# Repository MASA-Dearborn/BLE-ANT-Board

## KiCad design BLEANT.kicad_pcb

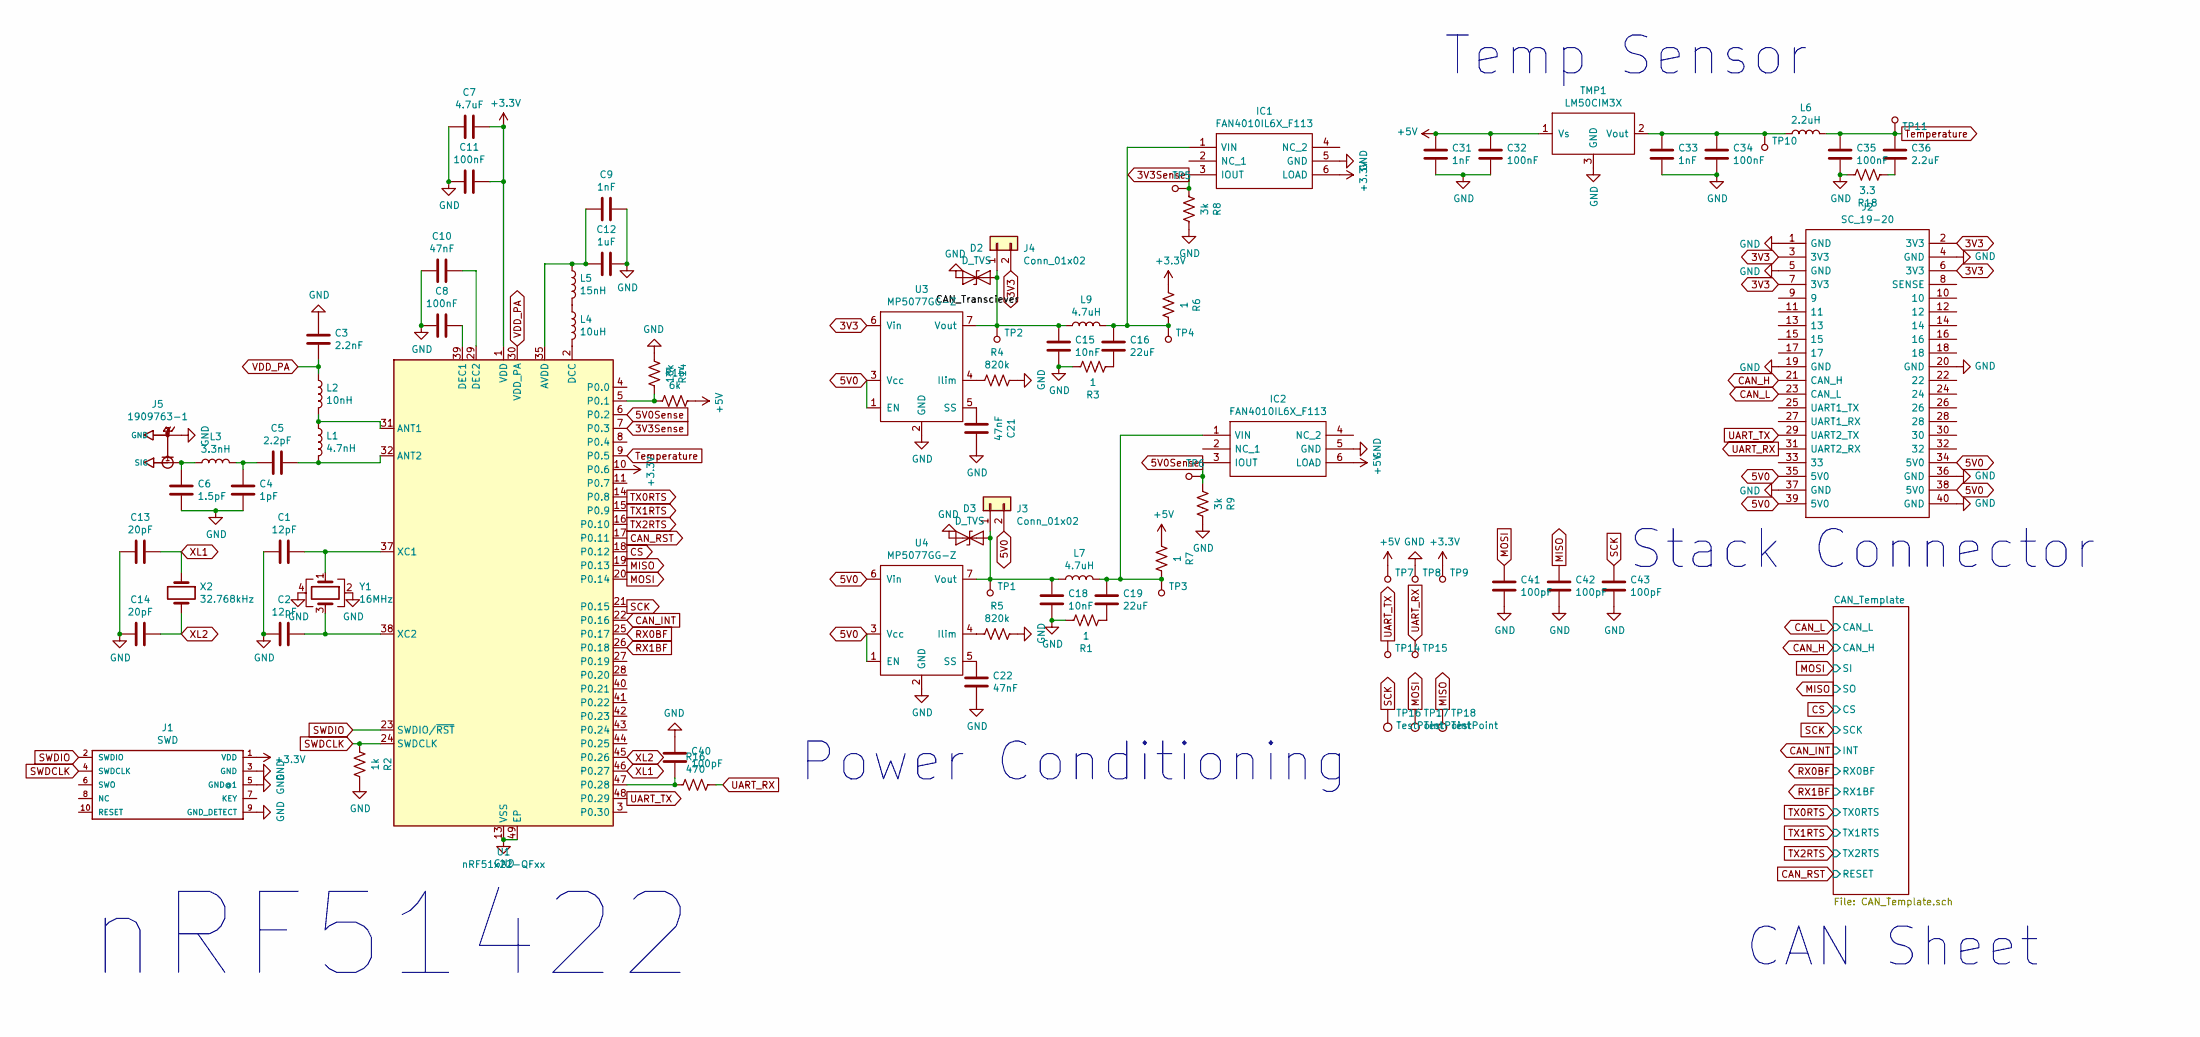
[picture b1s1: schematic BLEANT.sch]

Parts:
C1, C2: 12pF; C_0402_1005Metric
C3: 2.2nF; C_0402_1005Metric
C4: 1pF; C_0402_1005Metric
C5: 2.2pF; C_0402_1005Metric
C6: 1.5pF; C_0402_1005Metric
C7: 4.7uF; C_0402_1005Metric
C8, C11, C32, C34, C35: 100nF; C_0402_1005Metric
C9, C31, C33: 1nF; C_0402_1005Metric
C10, C21, C22: 47nF; C_0402_1005Metric
C12: 1uF; C_0402_1005Metric
C13, C14: 20pF; C_0402_1005Metric
C15, C18: 10nF; C_0402_1005Metric
C16, C19: 22uF; C_0805_2012Metric
C36: 2.2uF; C_0402_1005Metric
C40, C41, C42, C43: 100pF; C_0402_1005Metric
D2, D3: D_TVS; D_SOD-523
IC1, IC2: FAN4010IL6X_F113; 6-LEAD_MICROPAK; Manufacturer_Part_Number FAN4010IL6X_F113; Mouser Part Number 512-FAN4010IL6X_F113
J1: SWD; 2X10_BOXHEADER
J2: SC_19-20; Stack_Connector_2019_2020; Manufacturer_Part_Number TFC-120-32-F-D-A-K-TR
J3, J4: Conn_01x02; PinHeader_1x02_P2.54mm_Vertical
J5: 1909763-1; TE_1909763-1
L1: 4.7nH; L_0402_1005Metric
L2: 10nH; L_0402_1005Metric
L3: 3.3nH; L_0402_1005Metric
L4: 10uH; L_0603_1608Metric
L5: 15nH; L_0402_1005Metric
L6: 2.2uH; L_0402_1005Metric
L7, L9: 4.7uH; L_0805_2012Metric
R1, R3, R6, R7: 1; R_0402_1005Metric
R2: 1k; R_0402_1005Metric
R4, R5: 820k; R_0402_1005Metric
R8, R9: 3k; R_0402_1005Metric
R14: 10k; R_0402_1005Metric
R15: 6k; R_0402_1005Metric
R16: 470; R_0402_1005Metric
R18: 3.3; R_0402_1005Metric
TMP1: LM50CIM3X; SOT-23
TP1, TP2, TP3, TP4, TP5, TP6, TP7, TP8, TP9, TP10, TP11, TP14, TP15: 5029; PC_Test_Point_Mini_3.8x2.03mm; MPN 5029; Digi-Key_PN 36-5029CT-ND
TP16, TP17, TP18: TestPoint; TestPoint_Pad_2.0x2.0mm
U1: nRF51x22-QFxx; QFN-48-1EP_6x6mm_P0.4mm_EP4.6x4.6mm
U3, U4: MP5077GG-Z
X2: 32.768kHz; Crystal_SMD_MicroCrystal_CC7V-T1A-2Pin_3.2x1.5mm
Y1: 16MHz; Crystal_SMD_2520-4Pin_2.5x2.0mm

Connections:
3V3: J2.2 (3V3), J2.3 (3V3), J2.6 (3V3), J2.7 (3V3), J4.2, U3.6 (Vin), U3.11 (Vin)
3V3Sense: IC1.3 (IOUT), R8.1, TP5.1, U1.7 (P0.3)
5V0: J2.34 (5V0), J2.35 (5V0), J2.38 (5V0), J2.39 (5V0), J3.2, U3.1 (EN), U3.3 (Vcc), U4.1 (EN), U4.3 (Vcc), U4.6 (Vin), U4.11 (Vin)
5V0Sense: IC2.3 (IOUT), R9.1, TP6.1, U1.6 (P0.2)
+5V: C31.1, C32.1, IC2.6 (LOAD), R7.1, R15.1, TMP1.1 (Vs), TP7.1; also elsewhere on the board
CAN_H: J2.21 (CAN_H); also elsewhere on the board
CAN_INT: U1.22 (P0.16); also elsewhere on the board
CAN_L: J2.23 (CAN_L); also elsewhere on the board
CAN_RST: U1.17 (P0.11); also elsewhere on the board
CS: U1.18 (P0.12); also elsewhere on the board
GND: C1.2, C2.2, C3.1, C4.2, C6.2, C7.2, C8.2, C9.1, C10.2, C11.2, C12.1, C13.2, C14.2, C15.2, C18.2, C21.1, C22.1, C31.2, C32.2, C33.2, C34.2, C35.2, C40.2, C41.2, C42.2, C43.2, D2.2 (A2), D3.2 (A2), IC1.5 (GND), IC2.5 (GND), J1.3 (GND), J1.5 (GND@1), J1.9 (GND_DETECT), J2.1 (GND), J2.4 (GND), J2.5 (GND), J2.19 (GND), J2.20 (GND), J2.36 (GND), J2.37 (GND), J2.40 (GND), J5.2 (GND), J5.3 (GND), R1.2, R2.1, R3.2, R4.1, R5.1, R8.2, R9.2, R14.2, R18.2, TMP1.3 (GND), TP8.1, U1.13 (VSS), U1.33 (VSS), U1.34 (VSS), U1.49 (EP), U3.2 (GND), U4.2 (GND), Y1.2, Y1.4; also elsewhere on the board
MISO: C42.1, TP18.1, U1.19 (P0.13); also elsewhere on the board
MOSI: C41.1, TP17.1, U1.20 (P0.14); also elsewhere on the board
unnamed: C1.1, U1.37 (XC1), Y1.1
unnamed: C2.1, U1.38 (XC2), Y1.3
unnamed: C4.1, C5.2, L3.2
unnamed: C5.1, L1.2, U1.32 (ANT2)
unnamed: C6.1, J5.1 (SIG), L3.1
unnamed: C8.1, U1.39 (DEC1)
unnamed: C10.1, U1.29 (DEC2)
unnamed: C9.2, C12.2, L5.1, U1.35 (AVDD), U1.36 (AVDD)
unnamed: C15.1, D2.1 (A1), J4.1, L9.1, TP2.1, U3.7 (Vout), U3.8 (Vout), U3.9 (Vout), U3.10 (Vout)
unnamed: C16.1, IC1.1 (VIN), L9.2, R6.2, TP4.1
unnamed: C16.2, R3.1
unnamed: C18.1, D3.1 (A1), J3.1, L7.1, TP1.1, U4.7 (Vout), U4.8 (Vout), U4.9 (Vout), U4.10 (Vout)
unnamed: C19.1, IC2.1 (VIN), L7.2, R7.2, TP3.1
unnamed: C19.2, R1.1
unnamed: C21.2, U3.5 (SS)
unnamed: C22.2, U4.5 (SS)
unnamed: C33.1, C34.1, L6.1, TMP1.2 (Vout), TP10.1
unnamed: C36.2, R18.1
unnamed: C40.1, R16.2, U1.47 (P0.28)
unnamed: L1.1, L2.2, U1.31 (ANT1)
unnamed: L4.1, L5.2
unnamed: L4.2, U1.2 (DCC)
unnamed: R4.2, U3.4 (Ilim)
unnamed: R5.2, U4.4 (Ilim)
unnamed: R14.1, R15.2, U1.5 (P0.1)
RX0BF: U1.25 (P0.17); also elsewhere on the board
RX1BF: U1.26 (P0.18); also elsewhere on the board
SCK: C43.1, TP16.1, U1.21 (P0.15); also elsewhere on the board
SWDCLK: J1.4 (SWDCLK), R2.2, U1.24 (SWDCLK)
SWDIO: J1.2 (SWDIO), U1.23 (SWDIO/~RST)
TX0RTS: U1.14 (P0.8); also elsewhere on the board
TX1RTS: U1.15 (P0.9); also elsewhere on the board
TX2RTS: U1.16 (P0.10); also elsewhere on the board
Temperature: C35.1, C36.1, L6.2, TP11.1, U1.9 (P0.5)
UART_RX: J2.31 (UART2_RX), R16.1, TP15.1
UART_TX: J2.29 (UART2_TX), TP14.1, U1.48 (P0.29)
VDD_PA: C3.2, L2.1, U1.30 (VDD_PA)
XL1: C13.1, U1.46 (P0.27), X2.1
XL2: C14.1, U1.45 (P0.26), X2.2

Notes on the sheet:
nRF51422
Power Conditioning
Temp Sensor
Stack Connector
CAN Sheet

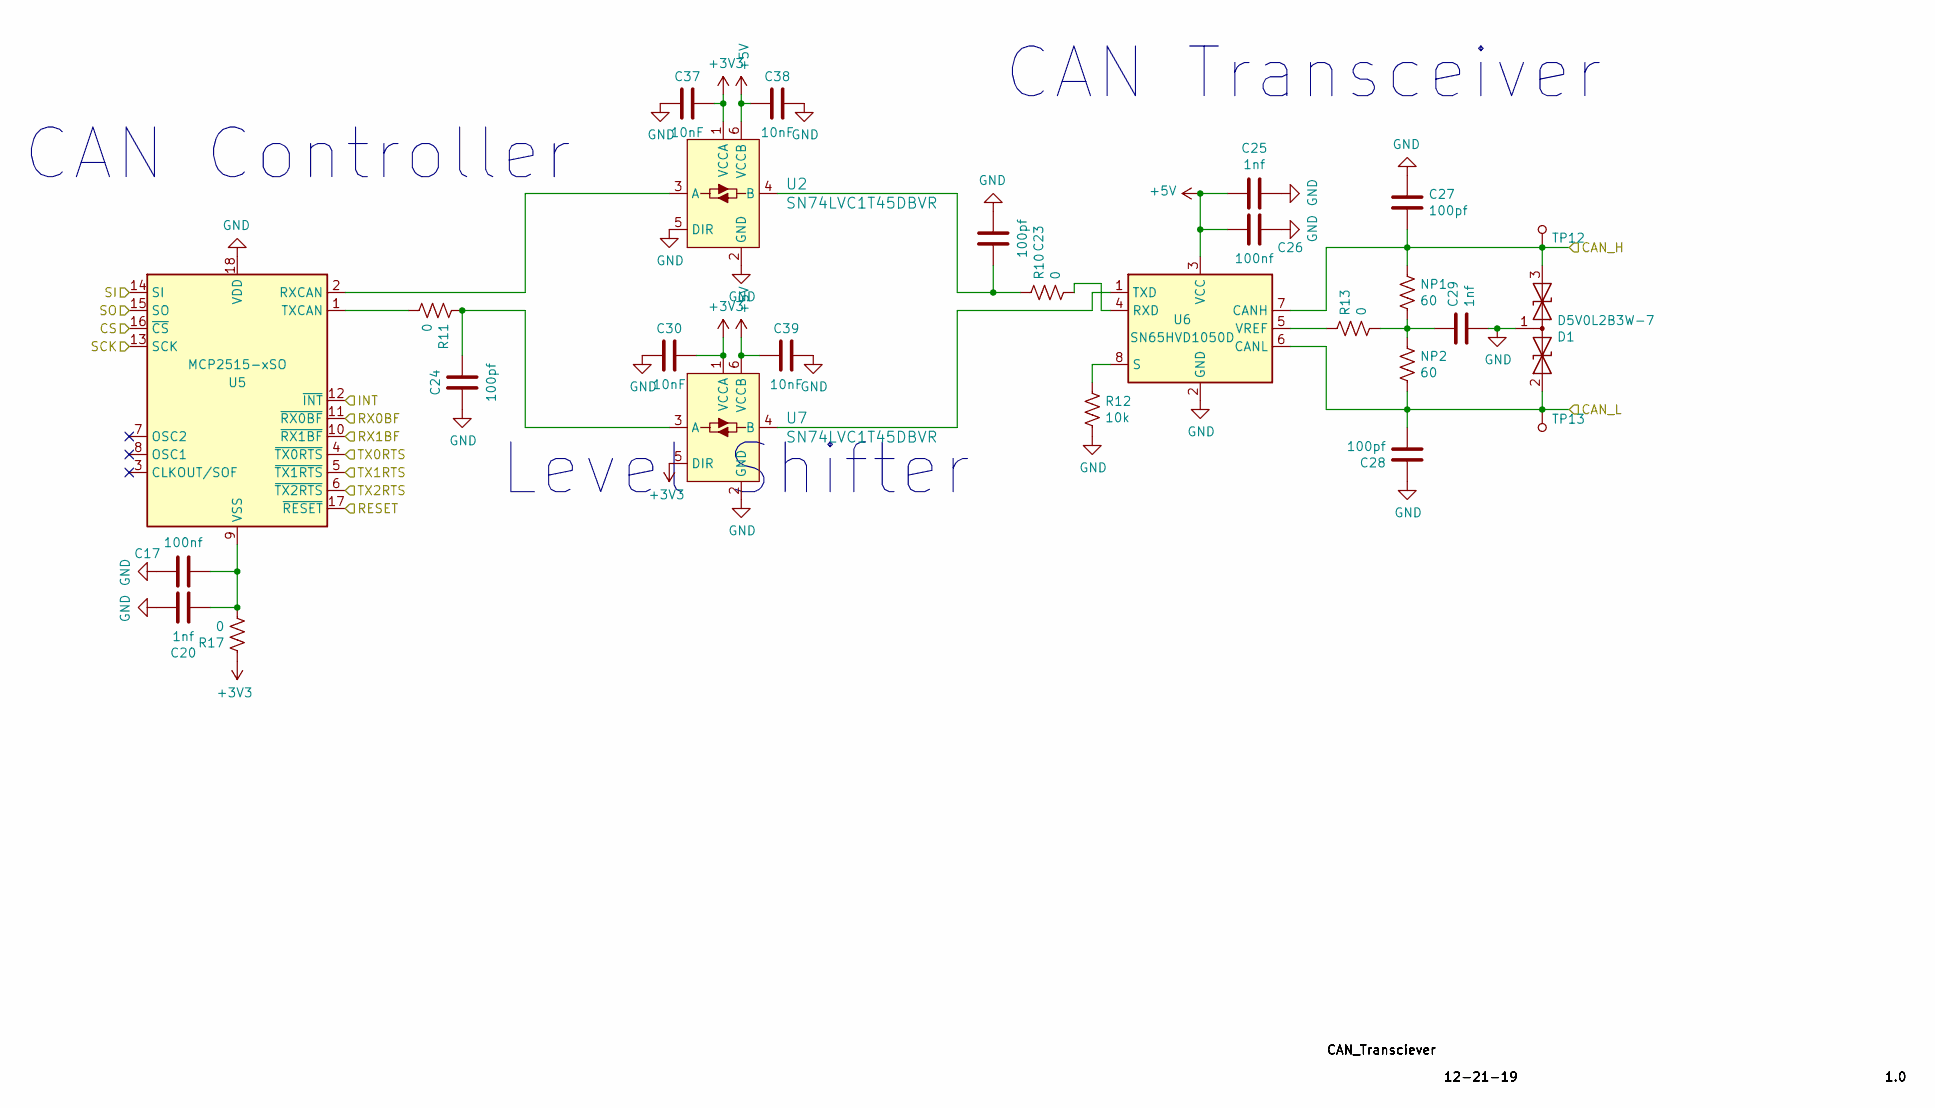
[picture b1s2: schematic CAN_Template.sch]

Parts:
C17, C26: 100nf; C_0402_1005Metric
C20, C25, C29: 1nf; C_0402_1005Metric
C23, C24, C27, C28: 100pf; C_0402_1005Metric
C30, C37, C38, C39: 10nF; C_0402_1005Metric
D1: D5V0L2B3W-7; SOT-23
NP1, NP2: 60; R_0402_1005Metric
R10, R11, R13, R17: 0; R_0402_1005Metric
R12: 10k; R_0402_1005Metric
TP12, TP13: 5029; PC_Test_Point_Mini_3.8x2.03mm; MPN 5029; Digi-Key_PN 36-5029CT-ND
U2, U7: SN74LVC1T45DBVR; SOT-23-6; MPN SN74LVC1T45DBVR; Digi-Key_PN 296-16843-1-ND
U5: MCP2515-xSO; SOIC-18W_7.5x11.6mm_P1.27mm
U6: SN65HVD1050D; SOIC-8_3.9x4.9mm_P1.27mm

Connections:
+5V: C25.2, C26.1, C38.1, C39.1, U2.6 (VCCB), U6.3 (VCC), U7.6 (VCCB); also elsewhere on the board
CAN_H: C27.2, D1.3 (A2), NP1.1, TP12.1, U6.7 (CANH); also elsewhere on the board
CAN_INT: U5.12 (~INT); also elsewhere on the board
CAN_L: C28.2, D1.2 (A1), NP2.2, TP13.1, U6.6 (CANL); also elsewhere on the board
CAN_RST: U5.17 (~RESET); also elsewhere on the board
CS: U5.16 (~CS); also elsewhere on the board
GND: C17.2, C20.1, C23.2, C24.1, C25.1, C26.2, C27.1, C28.1, C29.2, C30.1, C37.1, C38.2, C39.2, D1.1 (common), R12.2, U2.2 (GND), U2.5 (DIR), U5.18 (VDD), U6.2 (GND), U7.2 (GND); also elsewhere on the board
MISO: U5.15 (SO); also elsewhere on the board
MOSI: U5.14 (SI); also elsewhere on the board
unnamed: C17.1, C20.2, R17.2, U5.9 (VSS)
unnamed: C23.1, R10.1, U2.4 (B)
unnamed: C24.2, R11.1, U7.3 (A)
unnamed: C29.1, NP1.2, NP2.1, R13.2
unnamed: R10.2, U6.4 (RXD)
unnamed: R11.2, U5.1 (TXCAN)
unnamed: R12.1, U6.8 (S)
unnamed: R13.1, U6.5 (VREF)
unnamed: U2.3 (A), U5.2 (RXCAN)
unnamed: U6.1 (TXD), U7.4 (B)
RX0BF: U5.11 (~RX0BF); also elsewhere on the board
RX1BF: U5.10 (~RX1BF); also elsewhere on the board
SCK: U5.13 (SCK); also elsewhere on the board
TX0RTS: U5.4 (~TX0RTS); also elsewhere on the board
TX1RTS: U5.5 (~TX1RTS); also elsewhere on the board
TX2RTS: U5.6 (~TX2RTS); also elsewhere on the board

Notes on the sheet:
Level Shifter
CAN Transceiver
CAN Controller

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
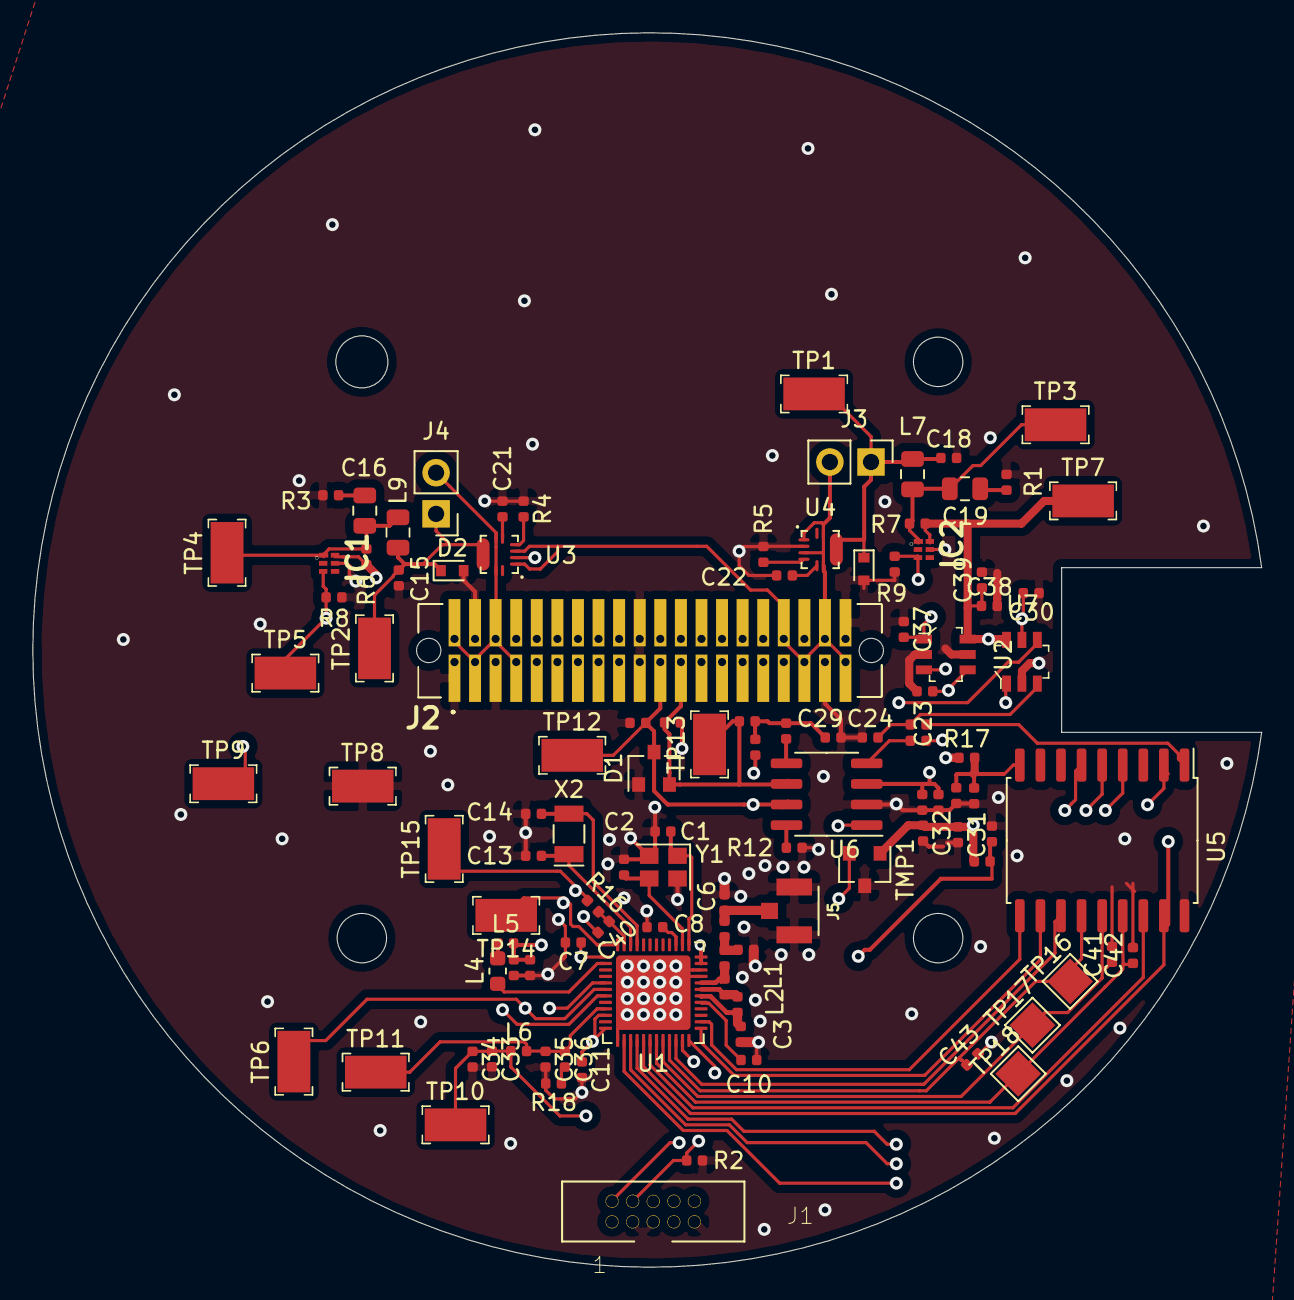
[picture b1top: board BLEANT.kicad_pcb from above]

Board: 4 copper layers, 75.8 x 76.2 mm, 109 parts (0 on the bottom side), 63 nets.

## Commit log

2019-12-15 nRF chip schematic done
2019-12-15 Added footprints to most components; left out RF parts
2019-12-21 Added stack template, temperature sensor, and crystal oscillator
2019-12-21 I did way too much for one commit
2019-12-22 added matching network. ruined half the other routing
2019-12-23 Placed all components. Need to add GPIO connections
2019-12-24 Connected all IO lines
2019-12-24 Added BOM
2019-12-25 Fixed my shit
2019-12-26 Added ground pours and stitching vias
2019-12-27 Made my chip not blow up with voltage dividers
2019-12-29 Changed filter and fixed CAN circuit
2019-12-29 Fixed some pads, added 3D model
2019-12-30 Added a level shifter
2020-01-12 Changed RF traces to 50Ohm microstrips
2020-01-17 Added filters and decoupling caps to temp sensor. Fixed pullup/down resistors on SWD
2020-01-17 Added the filter and other alterations to routing. Removed copper peninsulas and improved routing overall
2020-01-24 Added a metric ton of test points
2020-01-24 Added some filters and stuff
2020-02-18 Fixed clearances
2020-02-20 Fixed RF traces
